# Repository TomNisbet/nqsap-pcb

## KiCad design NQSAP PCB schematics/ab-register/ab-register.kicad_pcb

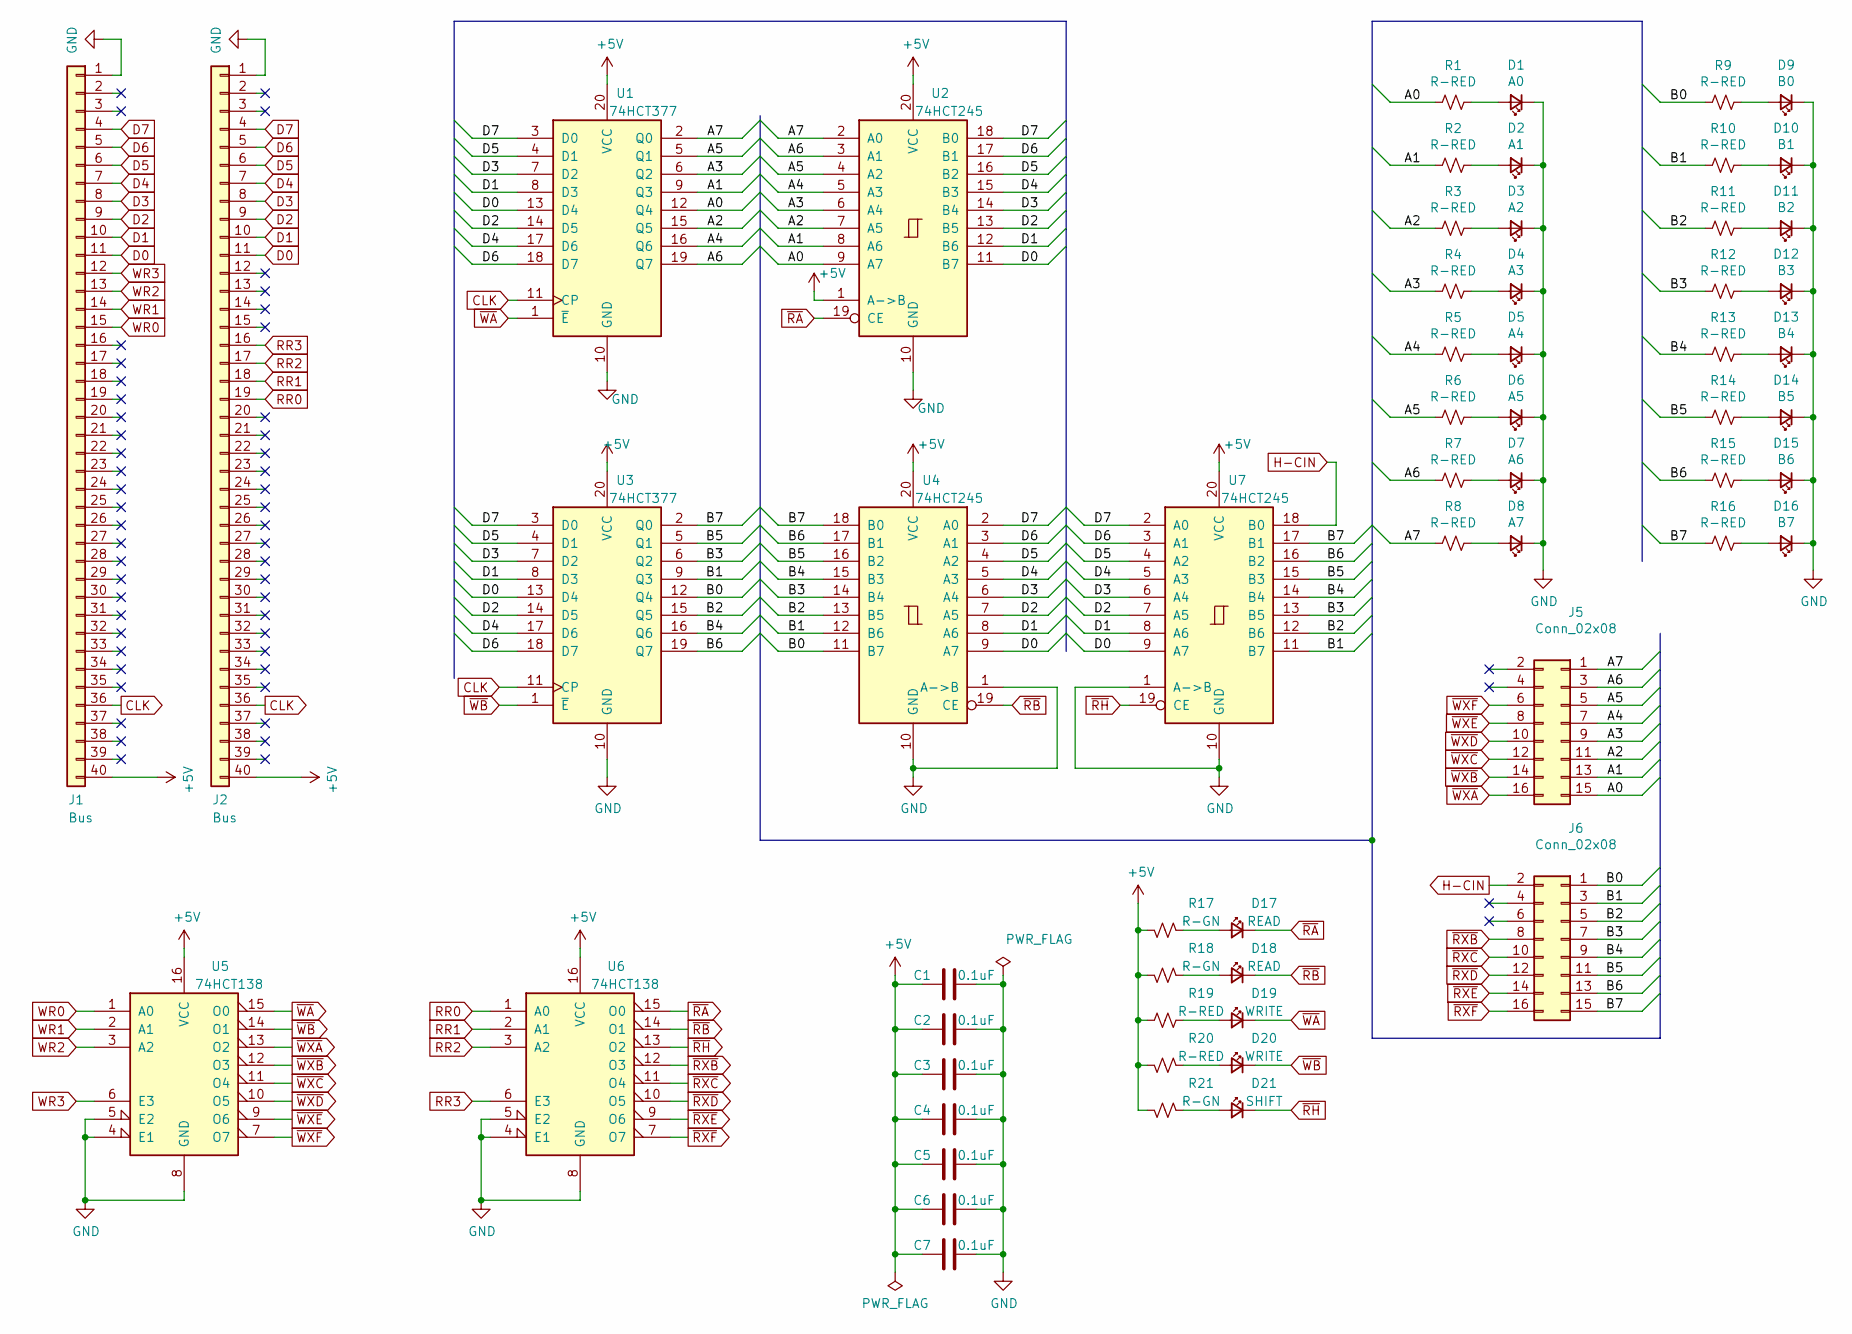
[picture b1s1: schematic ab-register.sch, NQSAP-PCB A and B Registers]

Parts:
C1, C2, C3, C4, C5, C6, C7: 0.1uF; C_0805_2012Metric_Pad1.18x1.45mm_HandSolder
D1: A0; LED_0805_2012Metric_Pad1.15x1.40mm_HandSolder
D2: A1; LED_0805_2012Metric_Pad1.15x1.40mm_HandSolder
D3: A2; LED_0805_2012Metric_Pad1.15x1.40mm_HandSolder
D4: A3; LED_0805_2012Metric_Pad1.15x1.40mm_HandSolder
D5: A4; LED_0805_2012Metric_Pad1.15x1.40mm_HandSolder
D6: A5; LED_0805_2012Metric_Pad1.15x1.40mm_HandSolder
D7: A6; LED_0805_2012Metric_Pad1.15x1.40mm_HandSolder
D8: A7; LED_0805_2012Metric_Pad1.15x1.40mm_HandSolder
D9: B0; LED_0805_2012Metric_Pad1.15x1.40mm_HandSolder
D10: B1; LED_0805_2012Metric_Pad1.15x1.40mm_HandSolder
D11: B2; LED_0805_2012Metric_Pad1.15x1.40mm_HandSolder
D12: B3; LED_0805_2012Metric_Pad1.15x1.40mm_HandSolder
D13: B4; LED_0805_2012Metric_Pad1.15x1.40mm_HandSolder
D14: B5; LED_0805_2012Metric_Pad1.15x1.40mm_HandSolder
D15: B6; LED_0805_2012Metric_Pad1.15x1.40mm_HandSolder
D16: B7; LED_0805_2012Metric_Pad1.15x1.40mm_HandSolder
D17, D18: READ; LED_0805_2012Metric_Pad1.15x1.40mm_HandSolder
D19, D20: WRITE; LED_0805_2012Metric_Pad1.15x1.40mm_HandSolder
D21: SHIFT; LED_0805_2012Metric_Pad1.15x1.40mm_HandSolder
J1, J2: Bus; PinHeader_1x40_P2.54mm_Vertical
J5, J6: Conn_02x08; PinHeader_2x08_P2.54mm_Vertical
R1, R2, R3, R4, R5, R6, R7, R8, R9, R10, R11, R12, R13, R14, R15, R16, R19, R20: R-RED; R_0805_2012Metric_Pad1.20x1.40mm_HandSolder
R17, R18, R21: R-GN; R_0805_2012Metric_Pad1.20x1.40mm_HandSolder
U1, U3: 74HCT377; DIP-20_W7.62mm
U2, U4, U7: 74HCT245; DIP-20_W7.62mm
U5, U6: 74HCT138; DIP-16_W7.62mm

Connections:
+5V: C1.2, C2.2, C3.2, C4.2, C5.2, C6.2, C7.2, J1.40, J2.40, R17.1, R18.1, R19.2, R20.1, R21.1, U1.20 (VCC), U2.1 (A->B), U2.20 (VCC), U3.20 (VCC), U4.20 (VCC), U5.16 (VCC), U6.16 (VCC), U7.20 (VCC)
/A0: J5.15, R1.2, U1.12 (Q4), U2.9 (A7)
/A1: J5.13, R2.2, U1.9 (Q3), U2.8 (A6)
/A2: J5.11, R3.2, U1.15 (Q5), U2.7 (A5)
/A3: J5.9, R4.2, U1.6 (Q2), U2.6 (A4)
/A4: J5.7, R5.2, U1.16 (Q6), U2.5 (A3)
/A5: J5.5, R6.2, U1.5 (Q1), U2.4 (A2)
/A6: J5.3, R7.2, U1.19 (Q7), U2.3 (A1)
/A7: J5.1, R8.2, U1.2 (Q0), U2.2 (A0)
/B0: J6.1, R9.2, U3.12 (Q4), U4.11 (B7)
/B1: J6.3, R10.2, U3.9 (Q3), U4.12 (B6), U7.11 (B7)
/B2: J6.5, R11.2, U3.15 (Q5), U4.13 (B5), U7.12 (B6)
/B3: J6.7, R12.2, U3.6 (Q2), U4.14 (B4), U7.13 (B5)
/B4: J6.9, R13.2, U3.16 (Q6), U4.15 (B3), U7.14 (B4)
/B5: J6.11, R14.2, U3.5 (Q1), U4.16 (B2), U7.15 (B3)
/B6: J6.13, R15.2, U3.19 (Q7), U4.17 (B1), U7.16 (B2)
/B7: J6.15, R16.2, U3.2 (Q0), U4.18 (B0), U7.17 (B1)
CLK: J1.36, J2.36, U1.11 (CP), U3.11 (CP)
D0: J1.11, J2.11, U1.13 (D4), U2.11 (B7), U3.13 (D4), U4.9 (A7), U7.9 (A7)
D1: J1.10, J2.10, U1.8 (D3), U2.12 (B6), U3.8 (D3), U4.8 (A6), U7.8 (A6)
D2: J1.9, J2.9, U1.14 (D5), U2.13 (B5), U3.14 (D5), U4.7 (A5), U7.7 (A5)
D3: J1.8, J2.8, U1.7 (D2), U2.14 (B4), U3.7 (D2), U4.6 (A4), U7.6 (A4)
D4: J1.7, J2.7, U1.17 (D6), U2.15 (B3), U3.17 (D6), U4.5 (A3), U7.5 (A3)
D5: J1.6, J2.6, U1.4 (D1), U2.16 (B2), U3.4 (D1), U4.4 (A2), U7.4 (A2)
D6: J1.5, J2.5, U1.18 (D7), U2.17 (B1), U3.18 (D7), U4.3 (A1), U7.3 (A1)
D7: J1.4, J2.4, U1.3 (D0), U2.18 (B0), U3.3 (D0), U4.2 (A0), U7.2 (A0)
GND: C1.1, C2.1, C3.1, C4.1, C5.1, C6.1, C7.1, D1.1 (K), D2.1 (K), D3.1 (K), D4.1 (K), D5.1 (K), D6.1 (K), D7.1 (K), D8.1 (K), D9.1 (K), D10.1 (K), D11.1 (K), D12.1 (K), D13.1 (K), D14.1 (K), D15.1 (K), D16.1 (K), J1.1, J2.1, U1.10 (GND), U2.10 (GND), U3.10 (GND), U4.1 (A->B), U4.10 (GND), U5.4 (E1), U5.5 (E2), U5.8 (GND), U6.4 (E1), U6.5 (E2), U6.8 (GND), U7.1 (A->B), U7.10 (GND)
H-CIN: J6.2, U7.18 (B0)
unnamed: D1.2 (A), R1.1
unnamed: D2.2 (A), R2.1
unnamed: D3.2 (A), R3.1
unnamed: D4.2 (A), R4.1
unnamed: D5.2 (A), R5.1
unnamed: D6.2 (A), R6.1
unnamed: D7.2 (A), R7.1
unnamed: D8.2 (A), R8.1
unnamed: D9.2 (A), R9.1
unnamed: D10.2 (A), R10.1
unnamed: D11.2 (A), R11.1
unnamed: D12.2 (A), R12.1
unnamed: D13.2 (A), R13.1
unnamed: D14.2 (A), R14.1
unnamed: D15.2 (A), R15.1
unnamed: D16.2 (A), R16.1
unnamed: D17.2 (A), R17.2
unnamed: D18.2 (A), R18.2
unnamed: D19.2 (A), R19.1
unnamed: D20.2 (A), R20.2
unnamed: D21.2 (A), R21.2
RR0: J2.19, U6.1 (A0)
RR1: J2.18, U6.2 (A1)
RR2: J2.17, U6.3 (A2)
RR3: J2.16, U6.6 (E3)
WR0: J1.15, U5.1 (A0)
WR1: J1.14, U5.2 (A1)
WR2: J1.13, U5.3 (A2)
WR3: J1.12, U5.6 (E3)
~RA: D17.1 (K), U2.19 (CE), U6.15 (O0)
~RB: D18.1 (K), U4.19 (CE), U6.14 (O1)
~RH: D21.1 (K), U6.13 (O2), U7.19 (CE)
~RXB: J6.8, U6.12 (O3)
~RXC: J6.10, U6.11 (O4)
~RXD: J6.12, U6.10 (O5)
~RXE: J6.14, U6.9 (O6)
~RXF: J6.16, U6.7 (O7)
~WA: D19.1 (K), U1.1 (~E), U5.15 (O0)
~WB: D20.1 (K), U3.1 (~E), U5.14 (O1)
~WXA: J5.16, U5.13 (O2)
~WXB: J5.14, U5.12 (O3)
~WXC: J5.12, U5.11 (O4)
~WXD: J5.10, U5.10 (O5)
~WXE: J5.8, U5.9 (O6)
~WXF: J5.6, U5.7 (O7)

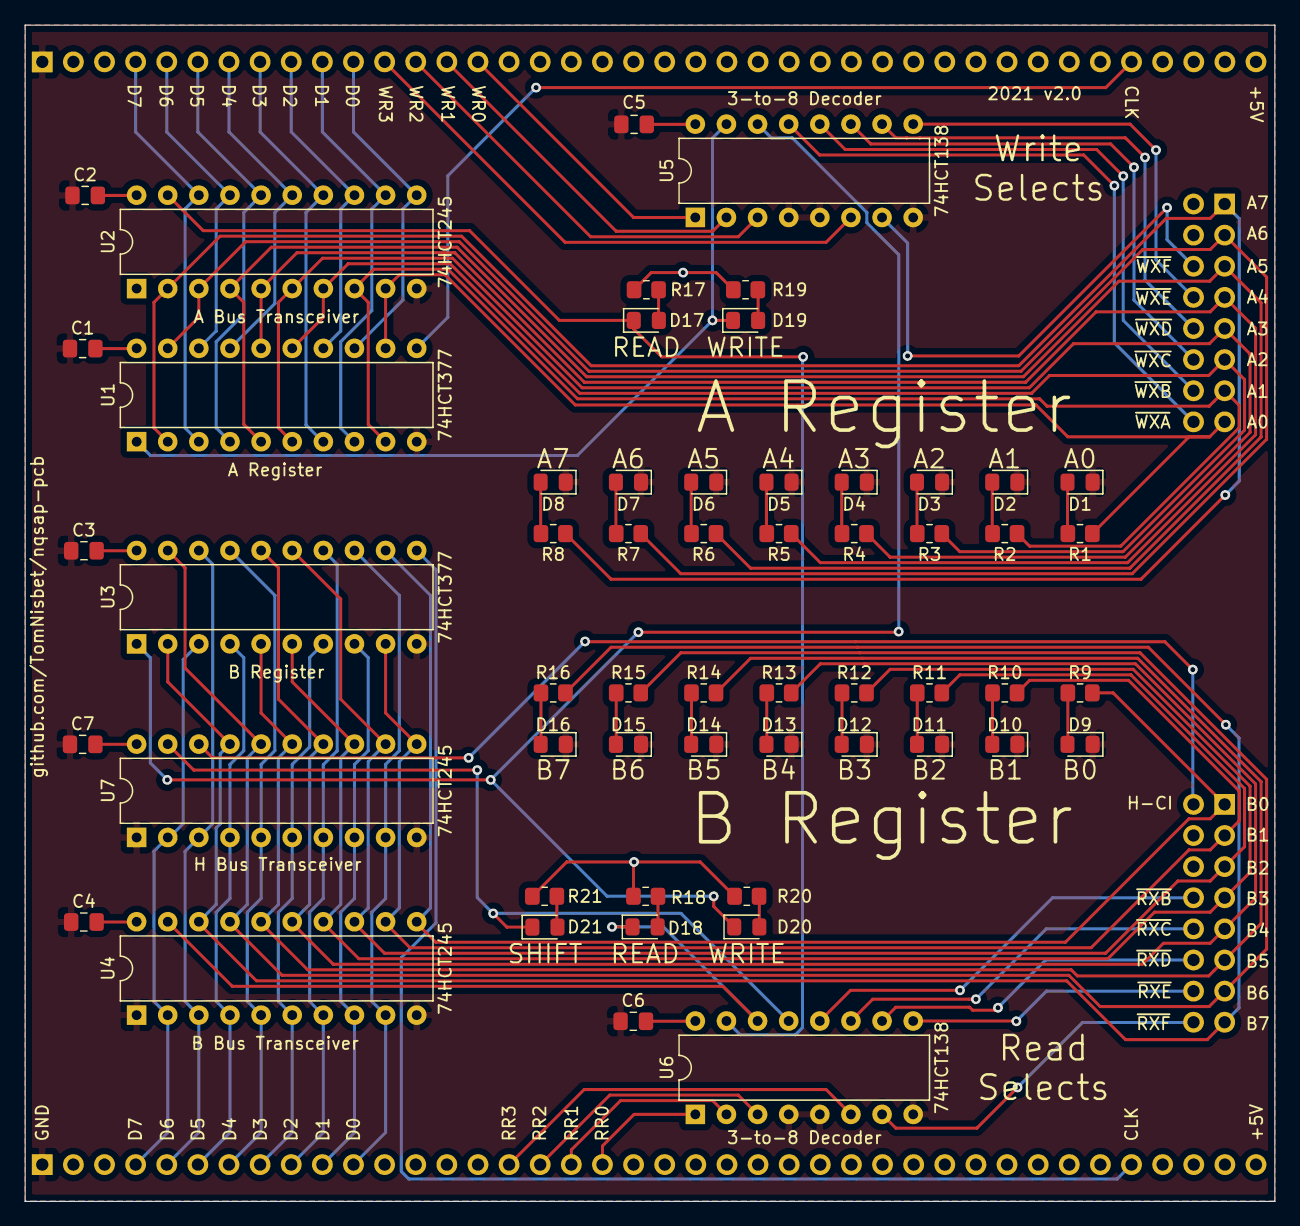
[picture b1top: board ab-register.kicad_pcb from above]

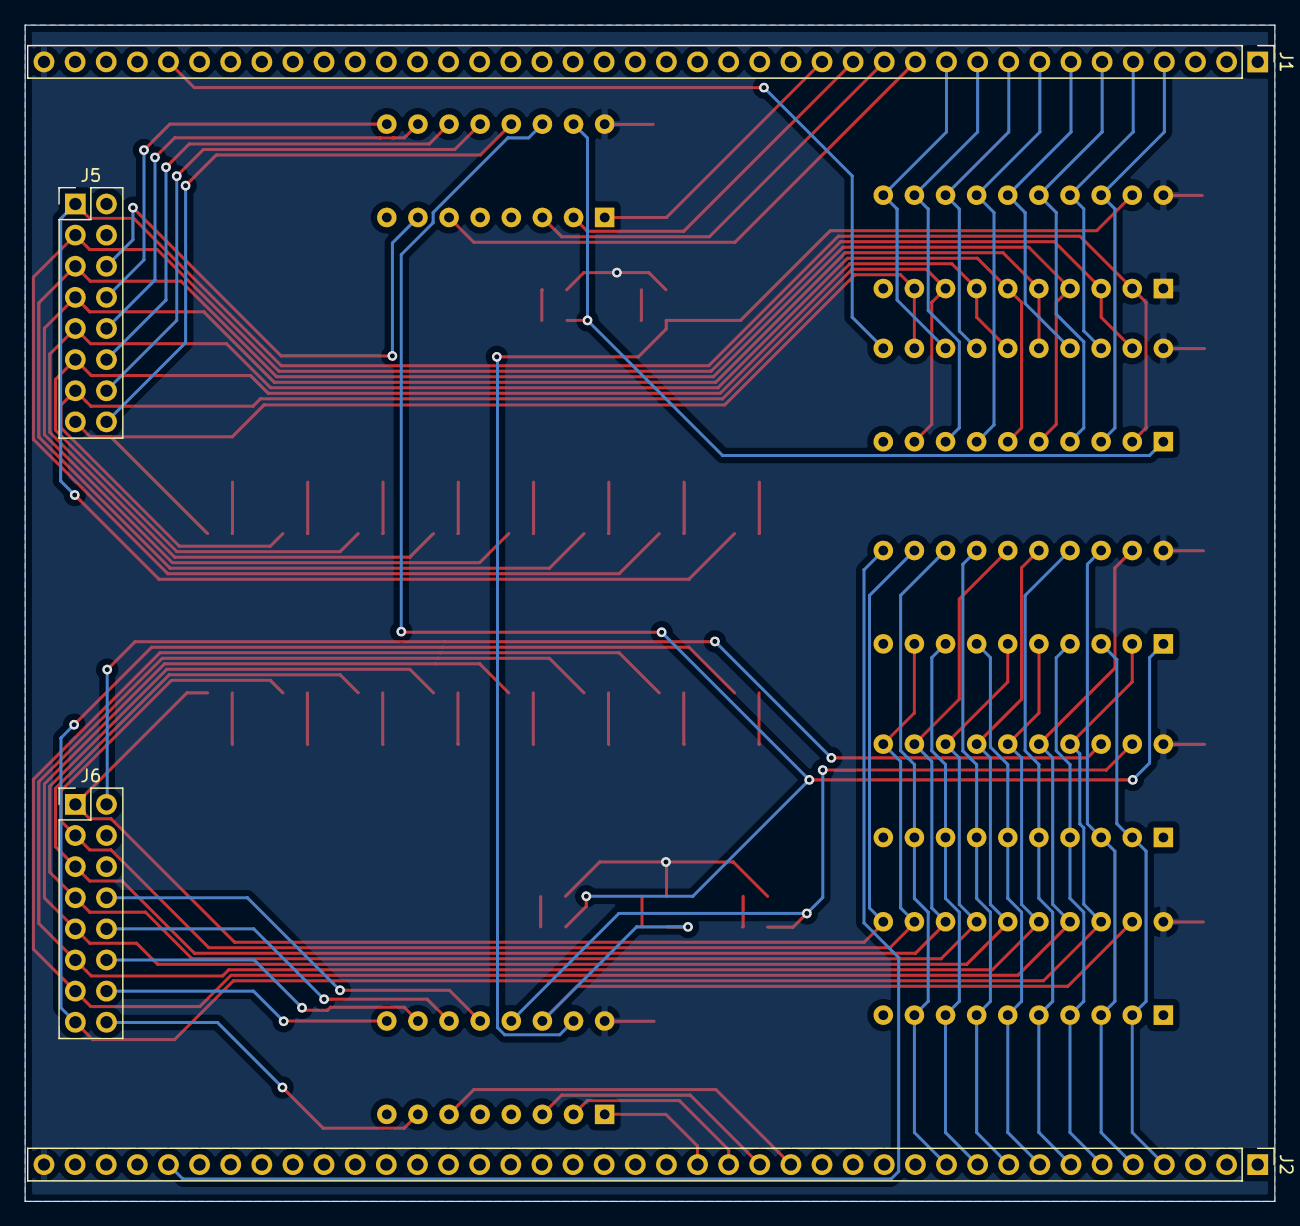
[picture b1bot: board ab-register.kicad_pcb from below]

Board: 2 copper layers, 102.0 x 96.0 mm, 60 parts (4 on the bottom side), 73 nets.

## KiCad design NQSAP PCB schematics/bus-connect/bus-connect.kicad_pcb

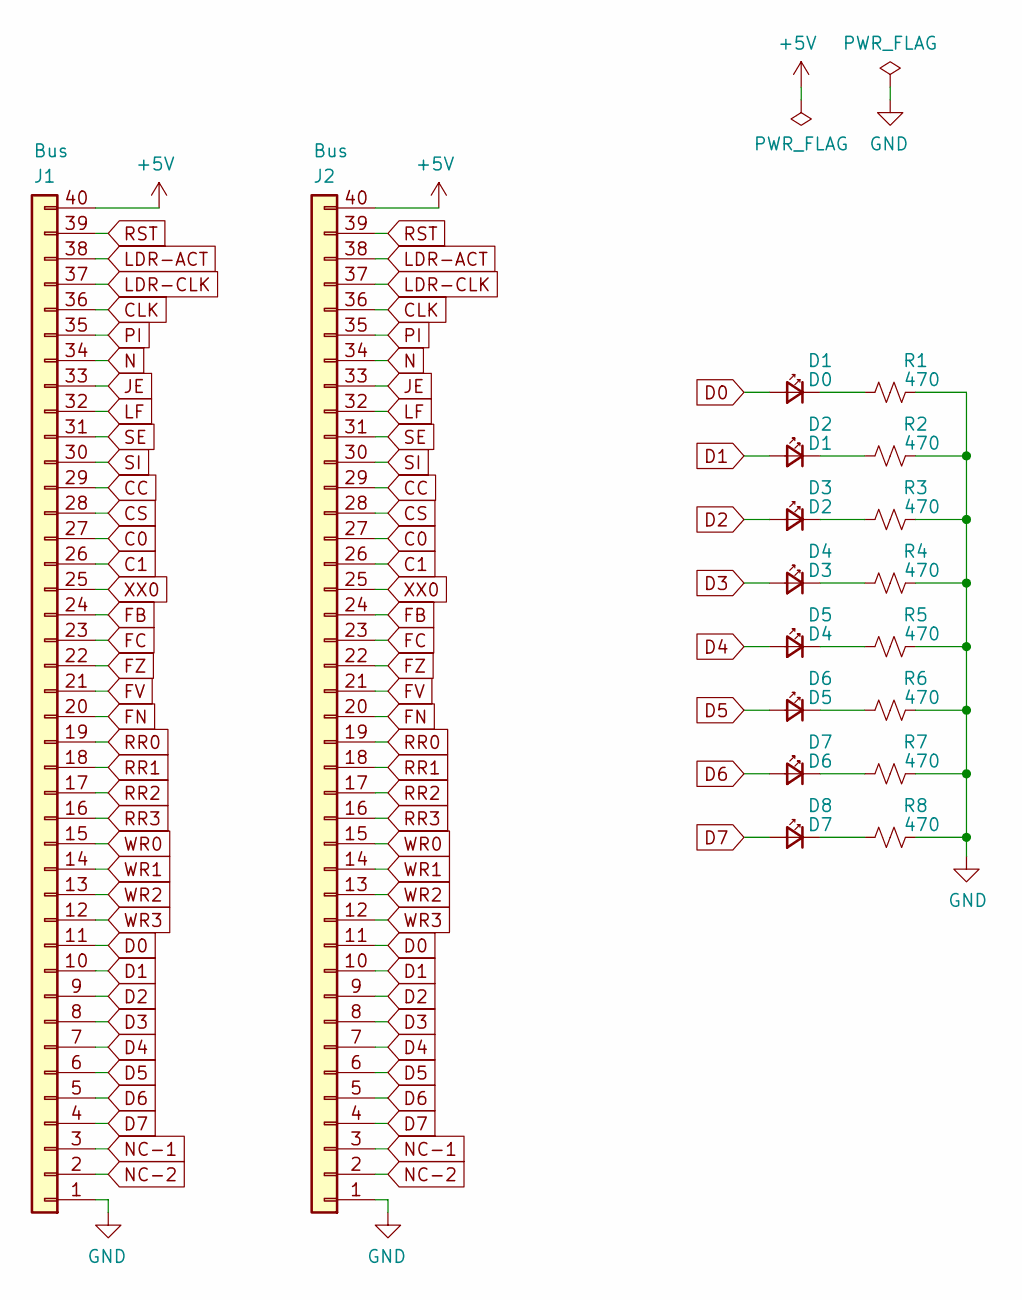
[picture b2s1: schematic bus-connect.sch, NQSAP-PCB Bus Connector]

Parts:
D1: D0; LED_0805_2012Metric_Pad1.15x1.40mm_HandSolder
D2: D1; LED_0805_2012Metric_Pad1.15x1.40mm_HandSolder
D3: D2; LED_0805_2012Metric_Pad1.15x1.40mm_HandSolder
D4: D3; LED_0805_2012Metric_Pad1.15x1.40mm_HandSolder
D5: D4; LED_0805_2012Metric_Pad1.15x1.40mm_HandSolder
D6: D5; LED_0805_2012Metric_Pad1.15x1.40mm_HandSolder
D7: D6; LED_0805_2012Metric_Pad1.15x1.40mm_HandSolder
D8: D7; LED_0805_2012Metric_Pad1.15x1.40mm_HandSolder
J1, J2: Bus; PinHeader_1x40_P2.54mm_Vertical
R1, R2, R3, R4, R5, R6, R7, R8: 470; R_0805_2012Metric_Pad1.20x1.40mm_HandSolder

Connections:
+5V: J1.40, J2.40
C0: J1.27, J2.27
C1: J1.26, J2.26
CC: J1.29, J2.29
CLK: J1.36, J2.36
CS: J1.28, J2.28
D0: D1.2 (A), J1.11, J2.11
D1: D2.2 (A), J1.10, J2.10
D2: D3.2 (A), J1.9, J2.9
D3: D4.2 (A), J1.8, J2.8
D4: D5.2 (A), J1.7, J2.7
D5: D6.2 (A), J1.6, J2.6
D6: D7.2 (A), J1.5, J2.5
D7: D8.2 (A), J1.4, J2.4
FB: J1.24, J2.24
FC: J1.23, J2.23
FN: J1.20, J2.20
FV: J1.21, J2.21
FZ: J1.22, J2.22
GND: J1.1, J2.1, R1.2, R2.2, R3.2, R4.2, R5.2, R6.2, R7.2, R8.2
JE: J1.33, J2.33
LDR-ACT: J1.38, J2.38
LDR-CLK: J1.37, J2.37
LF: J1.32, J2.32
N: J1.34, J2.34
NC-1: J1.3, J2.3
NC-2: J1.2, J2.2
unnamed: D1.1 (K), R1.1
unnamed: D2.1 (K), R2.1
unnamed: D3.1 (K), R3.1
unnamed: D4.1 (K), R4.1
unnamed: D5.1 (K), R5.1
unnamed: D6.1 (K), R6.1
unnamed: D7.1 (K), R7.1
unnamed: D8.1 (K), R8.1
PI: J1.35, J2.35
RR0: J1.19, J2.19
RR1: J1.18, J2.18
RR2: J1.17, J2.17
RR3: J1.16, J2.16
RST: J1.39, J2.39
SE: J1.31, J2.31
SI: J1.30, J2.30
WR0: J1.15, J2.15
WR1: J1.14, J2.14
WR2: J1.13, J2.13
WR3: J1.12, J2.12
XX0: J1.25, J2.25

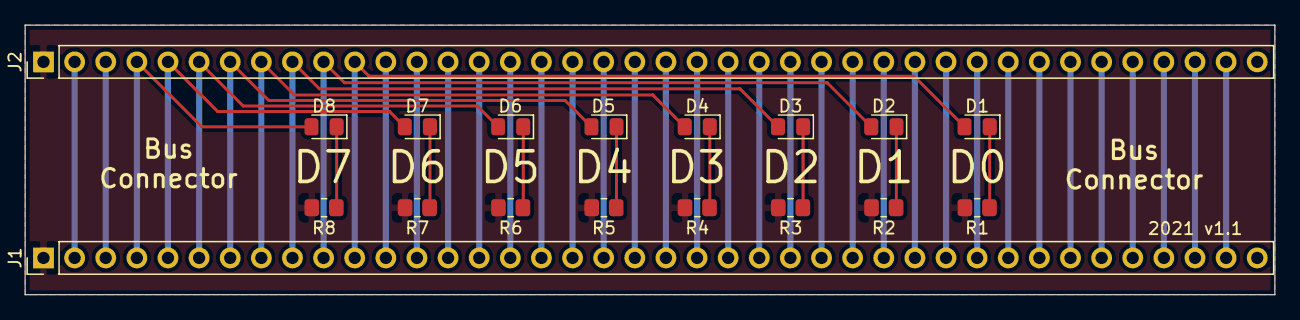
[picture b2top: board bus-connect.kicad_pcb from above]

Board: 2 copper layers, 102.0 x 22.0 mm, 18 parts (0 on the bottom side), 48 nets.

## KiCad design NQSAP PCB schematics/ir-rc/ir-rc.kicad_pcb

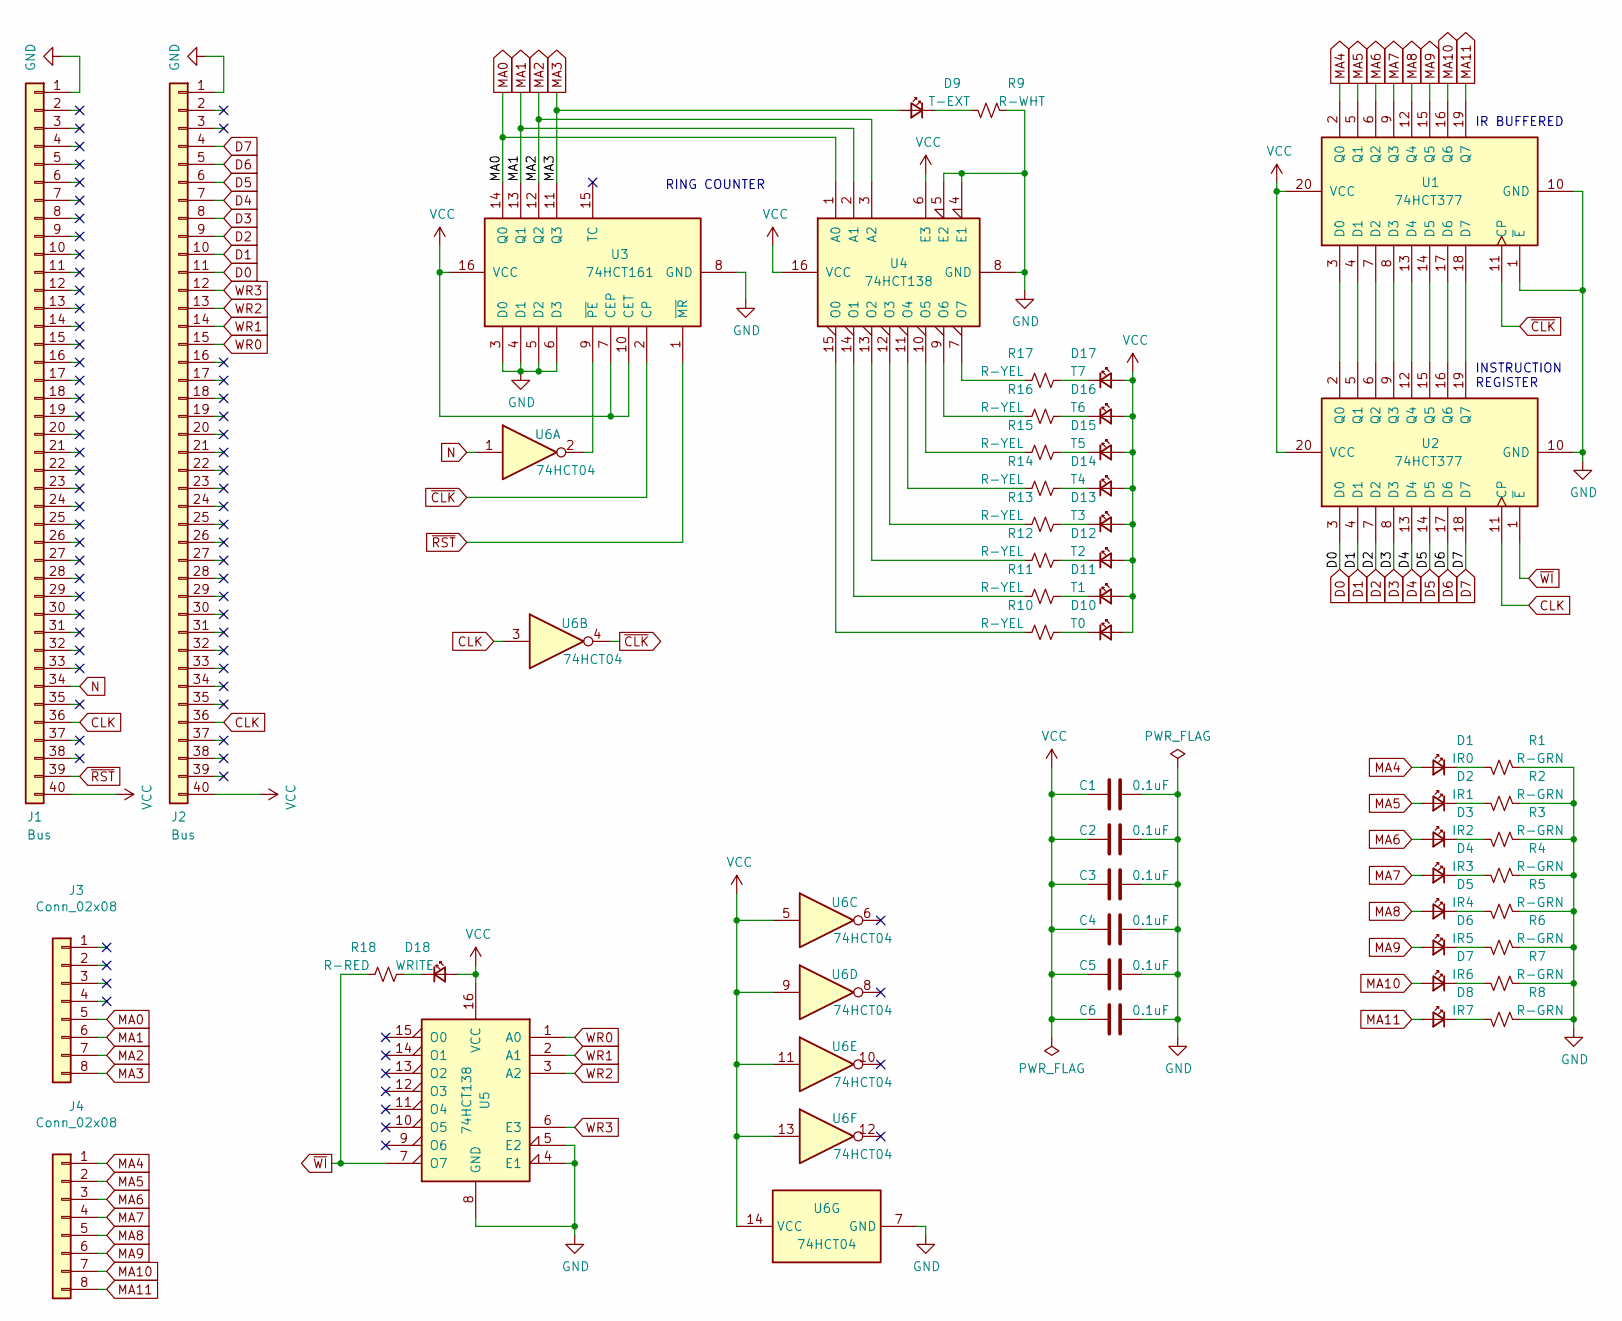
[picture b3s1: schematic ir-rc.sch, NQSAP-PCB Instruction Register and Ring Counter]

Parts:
C1, C2, C3, C4, C5, C6: 0.1uF; C_0805_2012Metric_Pad1.18x1.45mm_HandSolder
D1: IR0; LED_0805_2012Metric_Pad1.15x1.40mm_HandSolder
D2: IR1; LED_0805_2012Metric_Pad1.15x1.40mm_HandSolder
D3: IR2; LED_0805_2012Metric_Pad1.15x1.40mm_HandSolder
D4: IR3; LED_0805_2012Metric_Pad1.15x1.40mm_HandSolder
D5: IR4; LED_0805_2012Metric_Pad1.15x1.40mm_HandSolder
D6: IR5; LED_0805_2012Metric_Pad1.15x1.40mm_HandSolder
D7: IR6; LED_0805_2012Metric_Pad1.15x1.40mm_HandSolder
D8: IR7; LED_0805_2012Metric_Pad1.15x1.40mm_HandSolder
D9: T-EXT; LED_0805_2012Metric_Pad1.15x1.40mm_HandSolder
D10: T0; LED_0805_2012Metric_Pad1.15x1.40mm_HandSolder
D11: T1; LED_0805_2012Metric_Pad1.15x1.40mm_HandSolder
D12: T2; LED_0805_2012Metric_Pad1.15x1.40mm_HandSolder
D13: T3; LED_0805_2012Metric_Pad1.15x1.40mm_HandSolder
D14: T4; LED_0805_2012Metric_Pad1.15x1.40mm_HandSolder
D15: T5; LED_0805_2012Metric_Pad1.15x1.40mm_HandSolder
D16: T6; LED_0805_2012Metric_Pad1.15x1.40mm_HandSolder
D17: T7; LED_0805_2012Metric_Pad1.15x1.40mm_HandSolder
D18: WRITE; LED_0805_2012Metric_Pad1.15x1.40mm_HandSolder
J1, J2: Bus; PinHeader_1x40_P2.54mm_Vertical
J3, J4: Conn_02x08; PinHeader_1x08_P2.54mm_Vertical
R1, R2, R3, R4, R5, R6, R7, R8: R-GRN; R_0805_2012Metric_Pad1.20x1.40mm_HandSolder
R9: R-WHT; R_0805_2012Metric_Pad1.20x1.40mm_HandSolder
R10, R11, R12, R13, R14, R15, R16, R17: R-YEL; R_0805_2012Metric_Pad1.20x1.40mm_HandSolder
R18: R-RED; R_0805_2012Metric_Pad1.20x1.40mm_HandSolder
U1, U2: 74HCT377; DIP-20_W7.62mm
U3: 74HCT161; DIP-16_W7.62mm
U4, U5: 74HCT138; DIP-16_W7.62mm
U6: 74HCT04; DIP-14_W7.62mm

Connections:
CLK: J1.36, J2.36, U2.11 (CP), U6.3
D0: J2.11, U2.3 (D0)
D1: J2.10, U2.4 (D1)
D2: J2.9, U2.7 (D2)
D3: J2.8, U2.8 (D3)
D4: J2.7, U2.13 (D4)
D5: J2.6, U2.14 (D5)
D6: J2.5, U2.17 (D6)
D7: J2.4, U2.18 (D7)
GND: C1.1, C2.1, C3.1, C4.1, C5.1, C6.1, J1.1, J2.1, R1.2, R2.2, R3.2, R4.2, R5.2, R6.2, R7.2, R8.2, R9.1, U1.1 (~E), U1.10 (GND), U2.10 (GND), U3.3 (D0), U3.4 (D1), U3.5 (D2), U3.6 (D3), U3.8 (GND), U4.4 (E1), U4.5 (E2), U4.8 (GND), U5.4 (E1), U5.5 (E2), U5.8 (GND), U6.7 (GND)
MA0: J3.5, U3.14 (Q0), U4.1 (A0)
MA1: J3.6, U3.13 (Q1), U4.2 (A1)
MA2: J3.7, U3.12 (Q2), U4.3 (A2)
MA3: D9.2 (A), J3.8, U3.11 (Q3)
MA4: D1.2 (A), J4.1, U1.2 (Q0)
MA5: D2.2 (A), J4.2, U1.5 (Q1)
MA6: D3.2 (A), J4.3, U1.6 (Q2)
MA7: D4.2 (A), J4.4, U1.9 (Q3)
MA8: D5.2 (A), J4.5, U1.12 (Q4)
MA9: D6.2 (A), J4.6, U1.15 (Q5)
MA10: D7.2 (A), J4.7, U1.16 (Q6)
MA11: D8.2 (A), J4.8, U1.19 (Q7)
N: J1.34, U6.1
unnamed: D1.1 (K), R1.1
unnamed: D2.1 (K), R2.1
unnamed: D3.1 (K), R3.1
unnamed: D4.1 (K), R4.1
unnamed: D5.1 (K), R5.1
unnamed: D6.1 (K), R6.1
unnamed: D7.1 (K), R7.1
unnamed: D8.1 (K), R8.1
unnamed: D9.1 (K), R9.2
unnamed: D10.1 (K), R10.1
unnamed: D11.1 (K), R11.1
unnamed: D12.1 (K), R12.1
unnamed: D13.1 (K), R13.1
unnamed: D14.1 (K), R14.1
unnamed: D15.1 (K), R15.1
unnamed: D16.1 (K), R16.1
unnamed: D17.1 (K), R17.1
unnamed: D18.1 (K), R18.1
unnamed: R10.2, U4.15 (O0)
unnamed: R11.2, U4.14 (O1)
unnamed: R12.2, U4.13 (O2)
unnamed: R13.2, U4.12 (O3)
unnamed: R14.2, U4.11 (O4)
unnamed: R15.2, U4.10 (O5)
unnamed: R16.2, U4.9 (O6)
unnamed: R17.2, U4.7 (O7)
unnamed: U1.3 (D0), U2.2 (Q0)
unnamed: U1.4 (D1), U2.5 (Q1)
unnamed: U1.7 (D2), U2.6 (Q2)
unnamed: U1.8 (D3), U2.9 (Q3)
unnamed: U1.13 (D4), U2.12 (Q4)
unnamed: U1.14 (D5), U2.15 (Q5)
unnamed: U1.17 (D6), U2.16 (Q6)
unnamed: U1.18 (D7), U2.19 (Q7)
unnamed: U3.9 (~PE), U6.2
VCC: C1.2, C2.2, C3.2, C4.2, C5.2, C6.2, D10.2 (A), D11.2 (A), D12.2 (A), D13.2 (A), D14.2 (A), D15.2 (A), D16.2 (A), D17.2 (A), D18.2 (A), J1.40, J2.40, U1.20 (VCC), U2.20 (VCC), U3.7 (CEP), U3.10 (CET), U3.16 (VCC), U4.6 (E3), U4.16 (VCC), U5.16 (VCC), U6.5, U6.9, U6.11, U6.13, U6.14 (VCC)
WR0: J2.15, U5.1 (A0)
WR1: J2.14, U5.2 (A1)
WR2: J2.13, U5.3 (A2)
WR3: J2.12, U5.6 (E3)
~CLK: U1.11 (CP), U3.2 (CP), U6.4
~RST: J1.39, U3.1 (~MR)
~WI: R18.2, U2.1 (~E), U5.7 (O7)

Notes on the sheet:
INSTRUCTION REGISTER
RING COUNTER
IR BUFFERED

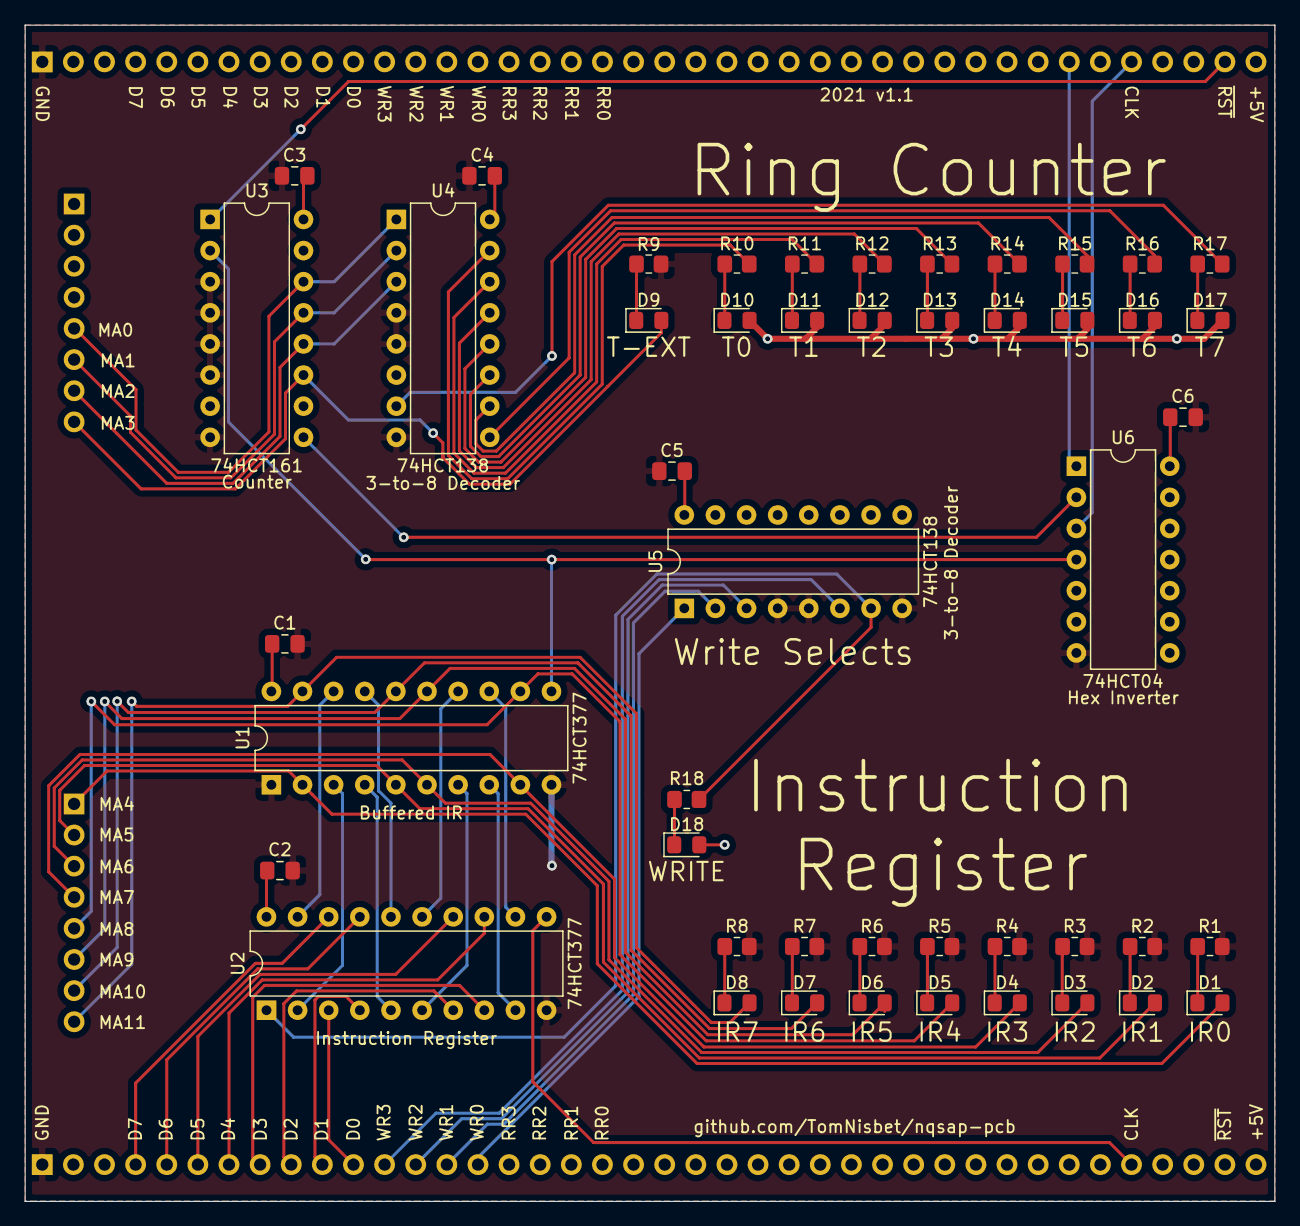
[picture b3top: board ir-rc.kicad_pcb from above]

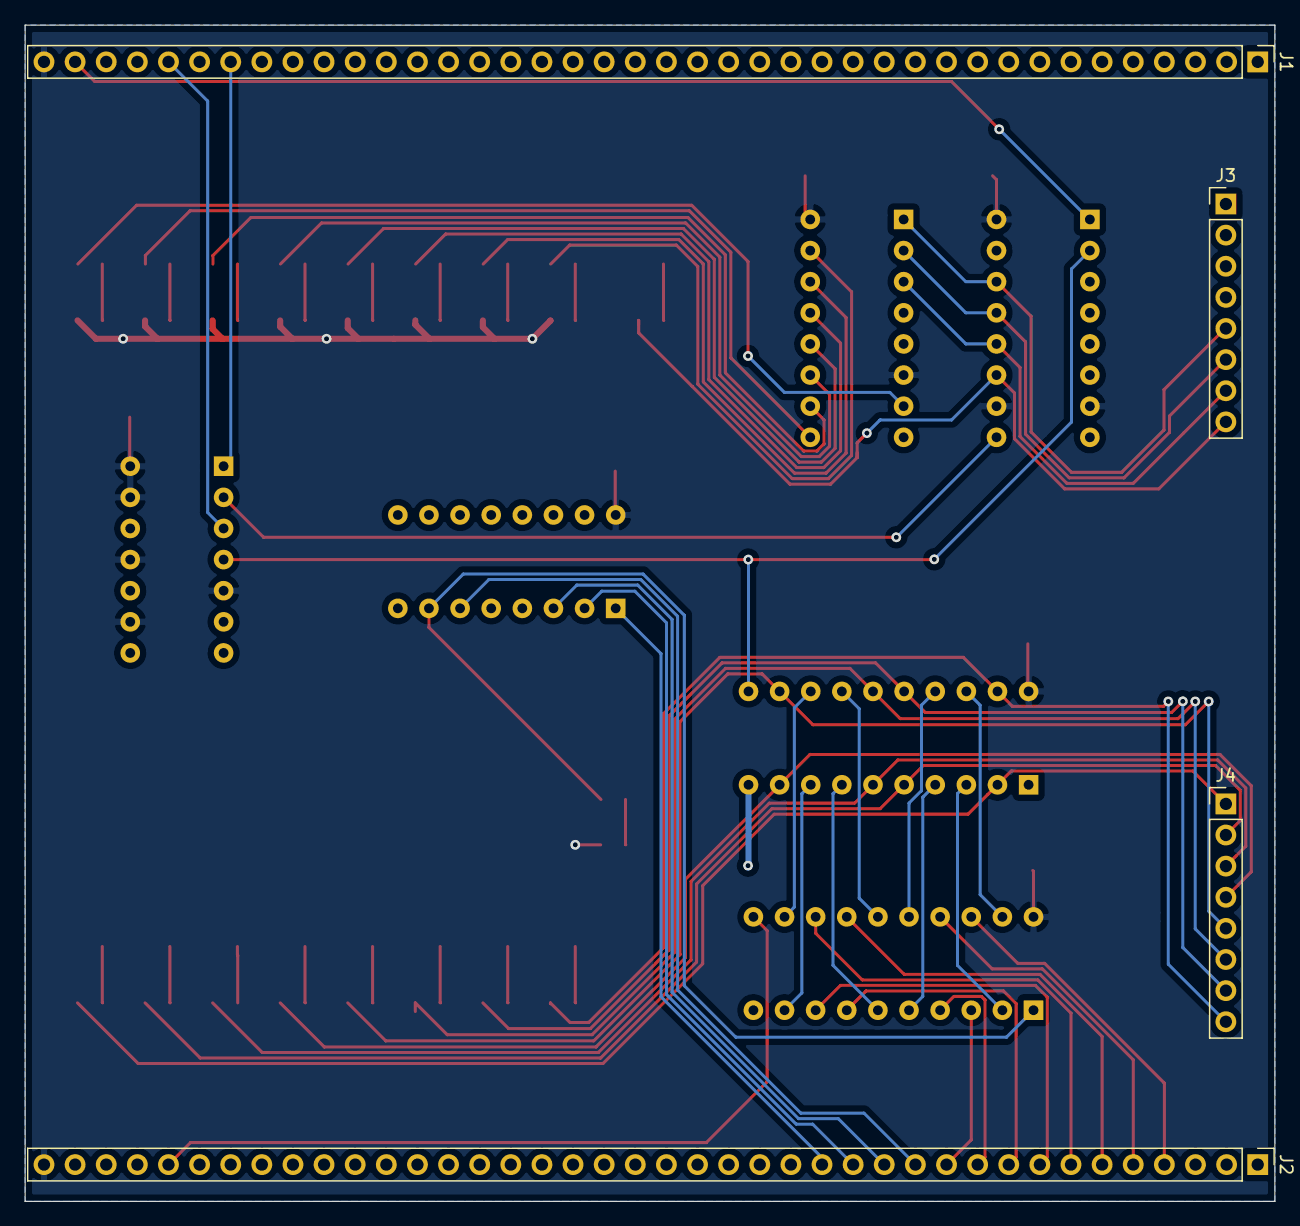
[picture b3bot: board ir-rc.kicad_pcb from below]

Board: 2 copper layers, 102.0 x 96.0 mm, 52 parts (4 on the bottom side), 66 nets.
